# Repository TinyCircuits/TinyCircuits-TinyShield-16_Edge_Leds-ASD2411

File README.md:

# TinyCircuits TinyShield 16 Edge LEDs
# ASD2411 Rev5

The design files are located under design_files/ for the TinyCircuits ASD2411 Rev 5 PCB.  This is a Tiny shield board (Square Version, 20mm x 20mm, or Circular 20mm diameter) that has a 16 LEDs around the border.

Format is in Cadsoft Eagle format - Eagle version 6.2 was used for the original design.

For more infomation on this, check out the product page at TinyCircuits.com: https://tinycircuits.com/collections/leds-displays/products/16-edge-led-tinyshield

# License:

Design by TinyCircuits.
All design files are released under the Creative Commons Attribution Share-Alike 3.0 License, see the following link for details: http://creativecommons.org/licenses/by-sa/3.0

All text above must be included in any redistribution or derived design

This project uses designs and concepts developed as part of the Arduino project and the LilyPad project.  The TinyCircuits design files themselves (schematics, PCB and libraries) are not directly derived from these works' design files and have been created new, however the concepts and basic architecture behind the TinyDuino and TinyLily products are derived and we thank the hard work of the organizations below for their contributions to open-source hardware:
  
Original Arduino Uno Design by Team Arduino

LilyPad Arduino Design by Leah Buechley and Sparkfun Electronics

Please support the open-source hardware community

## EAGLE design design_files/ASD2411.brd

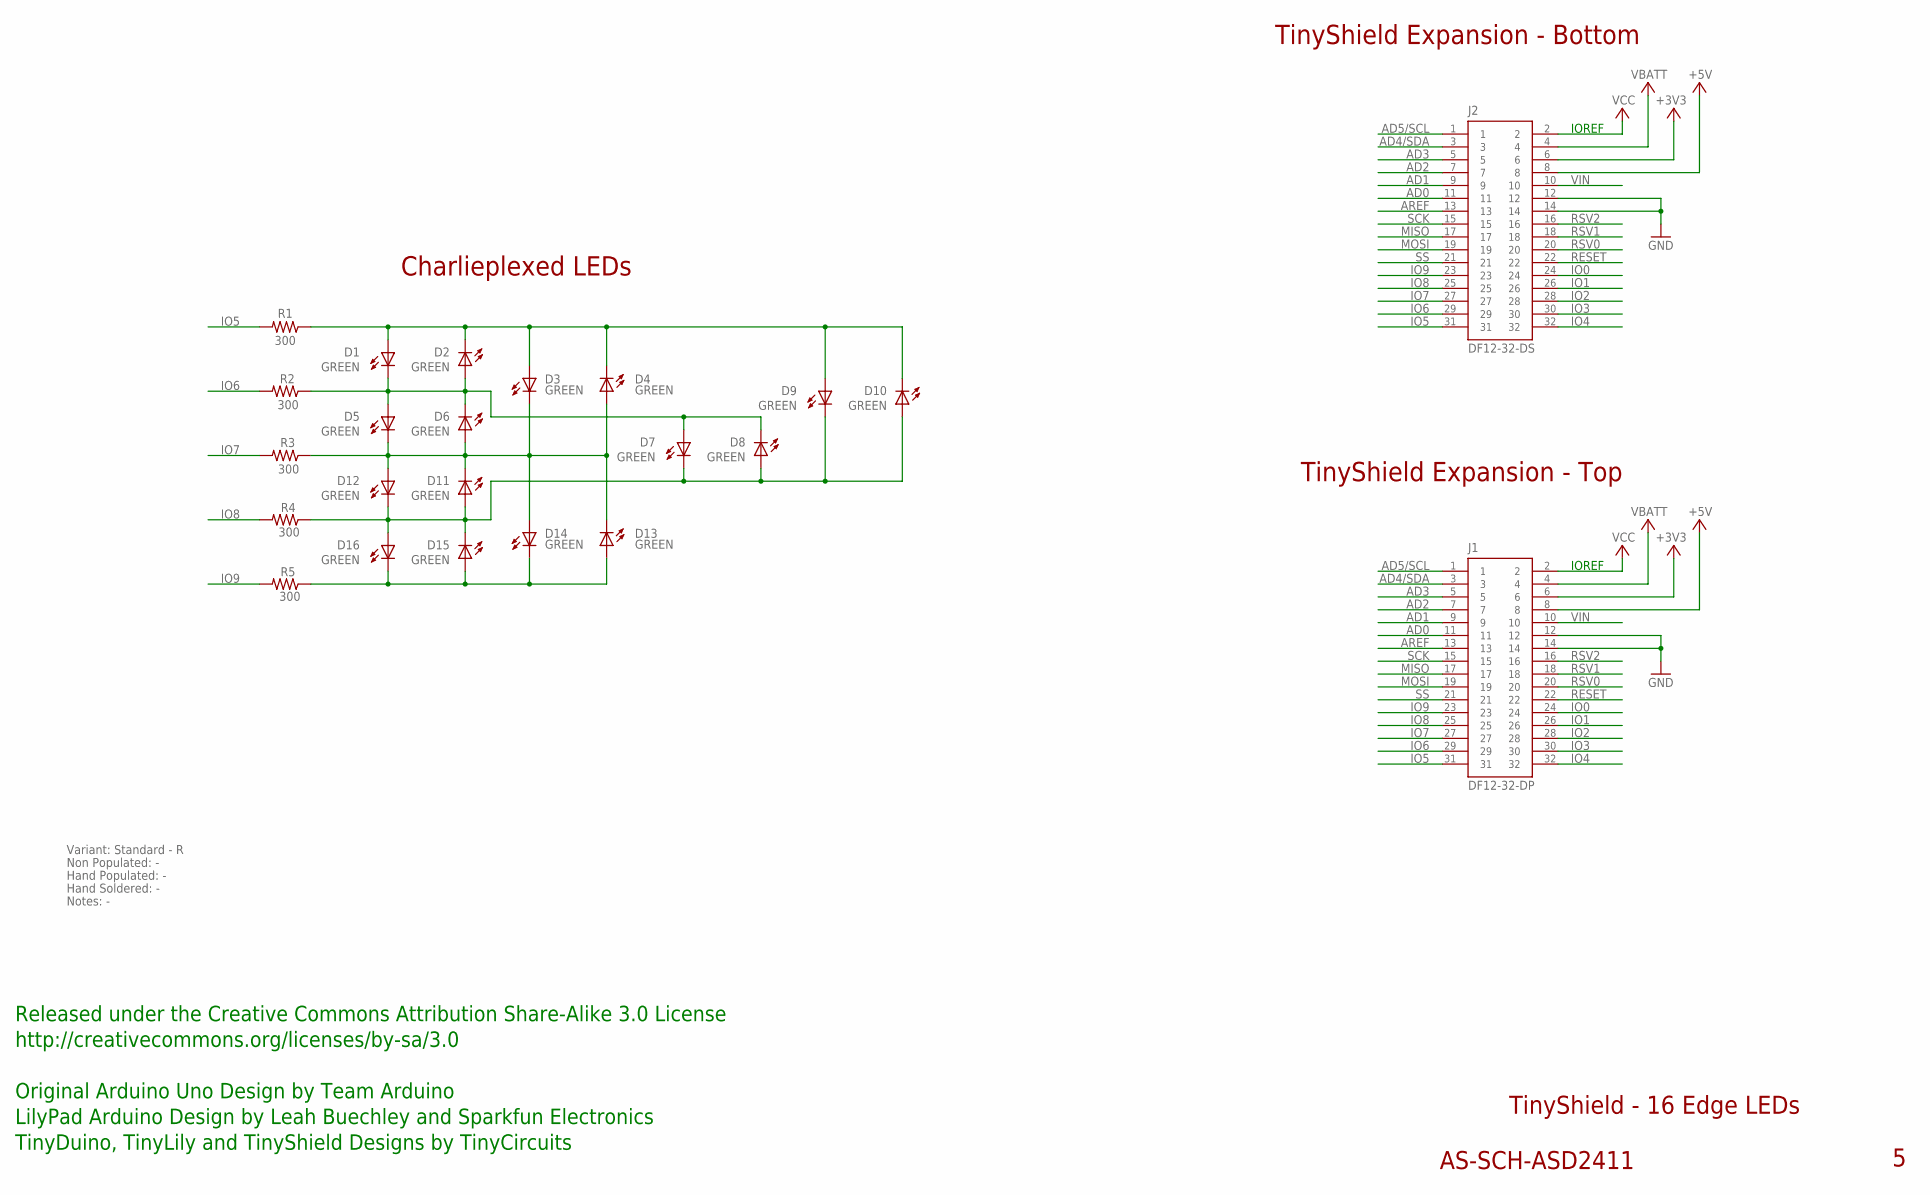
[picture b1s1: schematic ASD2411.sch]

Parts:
D1, D2, D3, D4, D5, D6, D7, D8, D9, D10, D11, D12, D13, D14, D15, D16: GREEN; LNJ_LED; PARTNO AS-ITM-00011
J1: DF12-32-DP; PARTNO AS-ITM-00015
J2: DF12-32-DS; PARTNO AS-ITM-00012
R1: 300; 0402; PARTNO AS-ITM-00016
R2, R3, R4, R5: 300; 0402

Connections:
+3V3: J1.6, J2.6
+5V: J1.8, J2.8
AD0: J1.11, J2.11
AD1: J1.9, J2.9
AD2: J1.7, J2.7
AD3: J1.5, J2.5
AD4/SDA: J1.3, J2.3
AD5/SCL: J1.1, J2.1
AREF: J1.13, J2.13
GND: J1.12, J1.14, J2.12, J2.14
IO0: J1.24, J2.24
IO1: J1.26, J2.26
IO2: J1.28, J2.28
IO3: J1.30, J2.30
IO4: J1.32, J2.32
IO5: J1.31, J2.31, R1.2
IO6: J1.29, J2.29, R2.2
IO7: J1.27, J2.27, R3.2
IO8: J1.25, J2.25, R4.2
IO9: J1.23, J2.23, R5.2
MISO: J1.17, J2.17
MOSI: J1.19, J2.19
unnamed: D1.C, D2.A, D5.A, D6.C, D7.A, D8.C, R2.1
unnamed: D1.A, D2.C, D3.A, D4.C, D9.A, D10.C, R1.1
unnamed: D3.C, D4.A, D5.C, D6.A, D11.C, D12.A, D13.C, D14.A, R3.1
unnamed: D7.C, D8.A, D9.C, D10.A, D11.A, D12.C, D15.C, D16.A, R4.1
unnamed: D13.A, D14.C, D15.A, D16.C, R5.1
RESET: J1.22, J2.22
RSV0: J1.20, J2.20
RSV1: J1.18, J2.18
RSV2: J1.16, J2.16
SCK: J1.15, J2.15
SS: J1.21, J2.21
VBATT: J1.4, J2.4
VCC: J1.2, J2.2
VIN: J1.10, J2.10

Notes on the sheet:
TinyShield Expansion - Bottom
Charlieplexed LEDs
TinyShield - 16 Edge LEDs
AS-SCH-ASD2411
TinyShield Expansion - Top
IOREF
Released under the Creative Commons Attribution Share-Alike 3.0 License
http://creativecommons.org/licenses/by-sa/3.0
LilyPad Arduino Design by Leah Buechley and Sparkfun Electronics
TinyDuino, TinyLily and TinyShield Designs by TinyCircuits
Original Arduino Uno Design by Team Arduino
Non Populated: -
Hand Populated: -
Hand Soldered: -
Variant: Standard - R
Notes: -

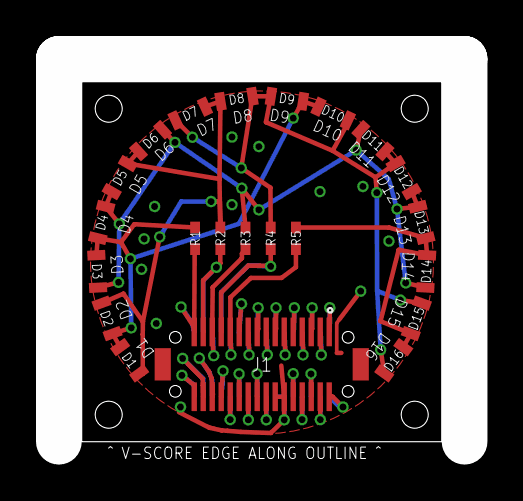
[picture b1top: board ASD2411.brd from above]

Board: 2 copper layers, 20.0 x 20.0 mm, 24 parts (1 on the bottom side), 36 nets.

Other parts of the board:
U$1: DOCFIELD-TINYCIRCUITS-PCB

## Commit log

2013-06-30 Updated project link
2013-12-24 Updated to Rev 4
2014-08-24 Updated Link
2019-01-04 update format and rev
2019-01-04 Added .zip file
2019-01-04 Removed .zip file
2019-01-07 Updated commenting
2019-01-07 updated comments
2019-01-11 added tutorial images
2019-01-11 added .zip files
2019-01-11 updated images
2019-05-20 updated naming
2019-05-20 changed naming
2020-02-11 image update
2020-07-28 Add CAD data
2020-08-14 Update CAD drawing
